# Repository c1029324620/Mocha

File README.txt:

Student Name: Xianjie Cao
Student #: 5004222179
Student Email: caox2@unlv.nevada.edu

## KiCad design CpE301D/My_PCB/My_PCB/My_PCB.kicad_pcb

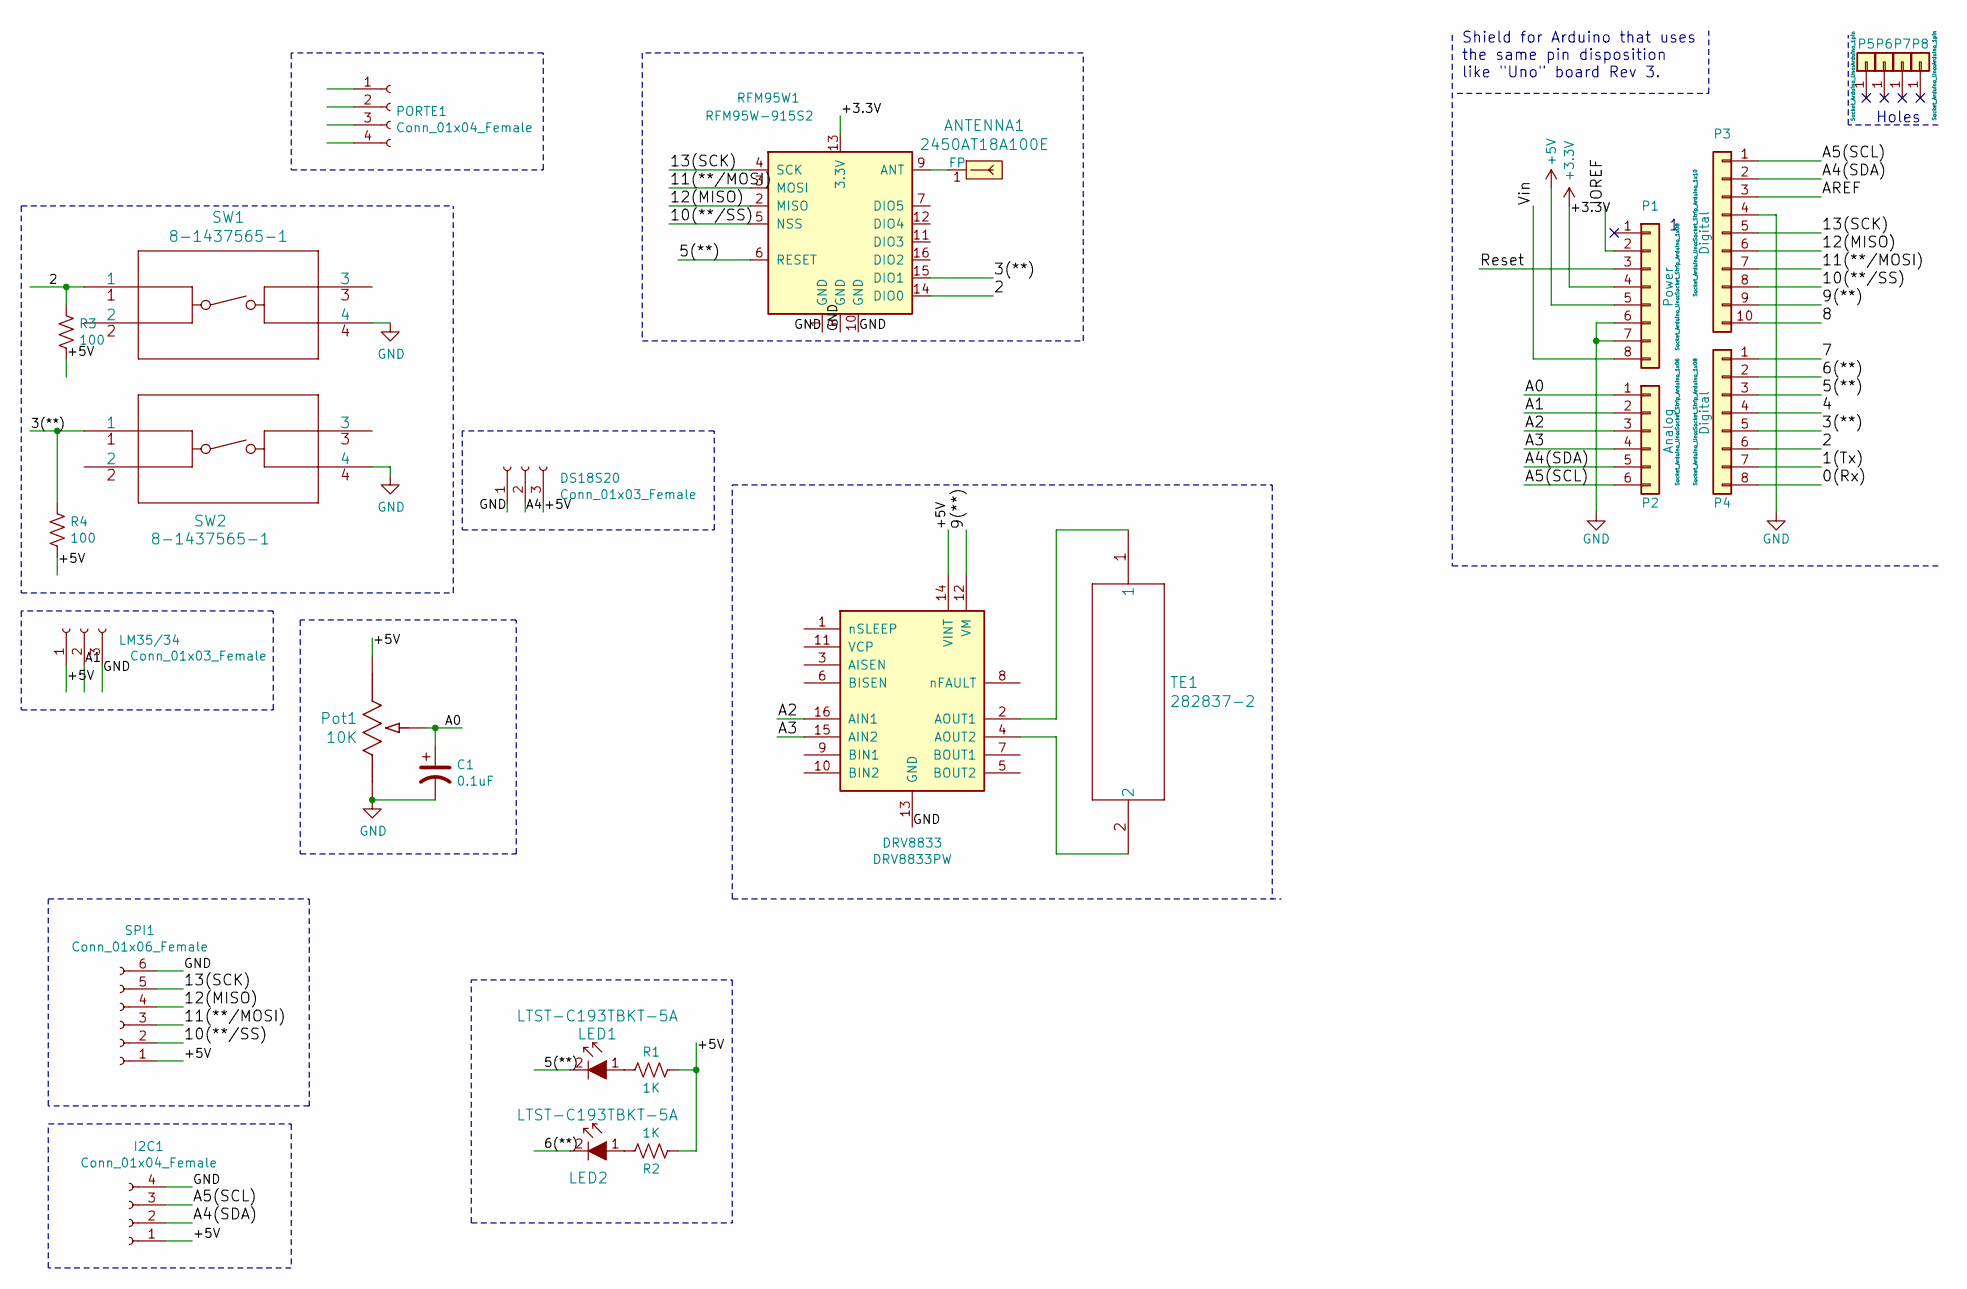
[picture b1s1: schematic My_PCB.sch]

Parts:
ANTENNA1: 2450AT18A100E; Antenna_1.6x3.2mm_2450AT18A100E; MPN 2450AT18A100E; Digi-Key_PN 712-1005-1-ND
C1: 0.1uF; CP_Radial_D5.0mm_P2.50mm
DRV8833: DRV8833PW; TSSOP-16_4.4x5mm_P0.65mm
DS18S20: Conn_01x03_Female; PinSocket_1x03_P2.54mm_Vertical
I2C1: Conn_01x04_Female; PinSocket_1x04_P2.54mm_Vertical
LED1, LED2: LTST-C193TBKT-5A; 0603; MPN LTST-C193TBKT-5A; Digi-Key_PN 160-1827-1-ND
LM35/34: Conn_01x03_Female; PinSocket_1x03_P2.54mm_Vertical
P1: Power; Socket_Strip_Arduino_1x08
P2: Analog; Socket_Strip_Arduino_1x06
P3: Digital; Socket_Strip_Arduino_1x10
P4: Digital; Socket_Strip_Arduino_1x08
P5, P6, P7, P8: CONN_01X01; Arduino_1pin
PORTE1: Conn_01x04_Female; PinSocket_1x04_P2.54mm_Vertical
Pot1: 10K; 3362P-1-103LF
R1, R2: 1K; R_0603_1608Metric_Pad1.05x0.95mm_HandSolder
R3, R4: 100; R_0603_1608Metric_Pad1.05x0.95mm_HandSolder
RFM95W1: RFM95W-915S2; HOPERF_RFM9XW_SMD
SPI1: Conn_01x06_Female; PinSocket_1x06_P2.54mm_Vertical
SW1, SW2: 8-1437565-1
TE1: 282837-2

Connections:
+3V3: P1.4, RFM95W1.13 (3.3V)
+5V: DRV8833.14 (VINT), DS18S20.3, I2C1.1, LM35/34.1, P1.5, Pot1.1, R1.1, R2.1, R3.2, R4.2, SPI1.1
/0(Rx): P4.8
/1(Tx): P4.7
/2: P4.6, R3.1, RFM95W1.14 (DIO0), SW1.1
/3(**): P4.5, R4.1, RFM95W1.15 (DIO1), SW2.1
/4: P4.4
/5(**): LED1.2, P4.3, RFM95W1.6 (RESET)
/6(**): LED2.2, P4.2
/7: P4.1
/8: P3.10
/9(**): DRV8833.12 (VM), P3.9
/10(**/SS): P3.8, RFM95W1.5 (NSS), SPI1.2
/11(**/MOSI): P3.7, RFM95W1.3 (MOSI), SPI1.3
/12(MISO): P3.6, RFM95W1.2 (MISO), SPI1.4
/13(SCK): P3.5, RFM95W1.4 (SCK), SPI1.5
/A0: C1.1, P2.1, Pot1.2
/A1: LM35/34.2, P2.2
/A2: DRV8833.16 (AIN1), P2.3
/A3: DRV8833.15 (AIN2), P2.4
/A4: DS18S20.2
/A4(SDA): I2C1.2, P2.5, P3.2
/A5(SCL): I2C1.3, P2.6, P3.1
/AREF: P3.3
/IOREF: P1.2
/Reset: P1.3
/Vin: P1.8
GND: C1.2, DRV8833.13 (GND), DS18S20.1, I2C1.4, LM35/34.3, P1.6, P1.7, P3.4, Pot1.3, RFM95W1.1 (GND), RFM95W1.8 (GND), RFM95W1.10 (GND), SPI1.6, SW1.4, SW2.4
unnamed: ANTENNA1.1 (FP), RFM95W1.9 (ANT)
unnamed: DRV8833.2 (AOUT1), TE1.1
unnamed: DRV8833.4 (AOUT2), TE1.2
unnamed: LED1.1, R1.2
unnamed: LED2.1, R2.2

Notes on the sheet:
Holes
Shield for Arduino that uses the same pin disposition like "Uno" board Rev 3.

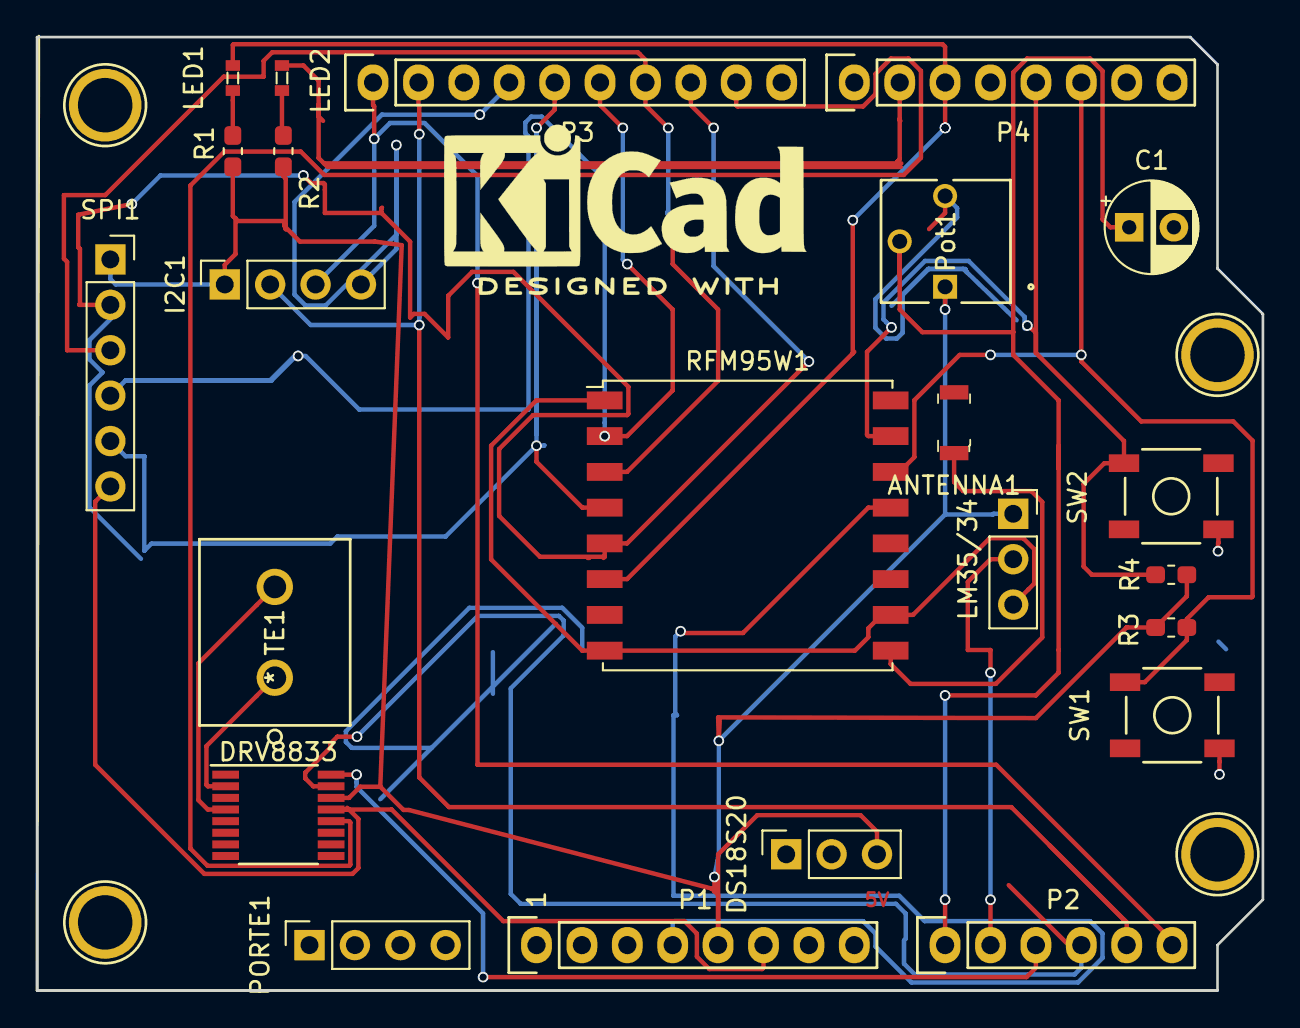
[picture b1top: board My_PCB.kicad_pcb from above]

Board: 2 copper layers, 68.6 x 53.3 mm, 27 parts (0 on the bottom side), 23 nets.

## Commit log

2020-01-22 Rename README.md to README.txt
2020-01-22 Create DA
2020-01-27 Design Assignment 1A
2020-01-27 github submission
2020-02-11 DA1A
2020-02-19 DA1B
2020-02-25 DA_2A
2020-02-28 DA2B
2020-03-06 DA2C
2020-03-11 DA3A
2020-03-15 DA3B
2020-03-20 Midterm
2020-03-31 DA4A
2020-04-07 DA4B
2020-05-01 301D

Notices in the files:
parts and their libraries:
Copyright 2016 Accelerated Designs. All rights reserved.
